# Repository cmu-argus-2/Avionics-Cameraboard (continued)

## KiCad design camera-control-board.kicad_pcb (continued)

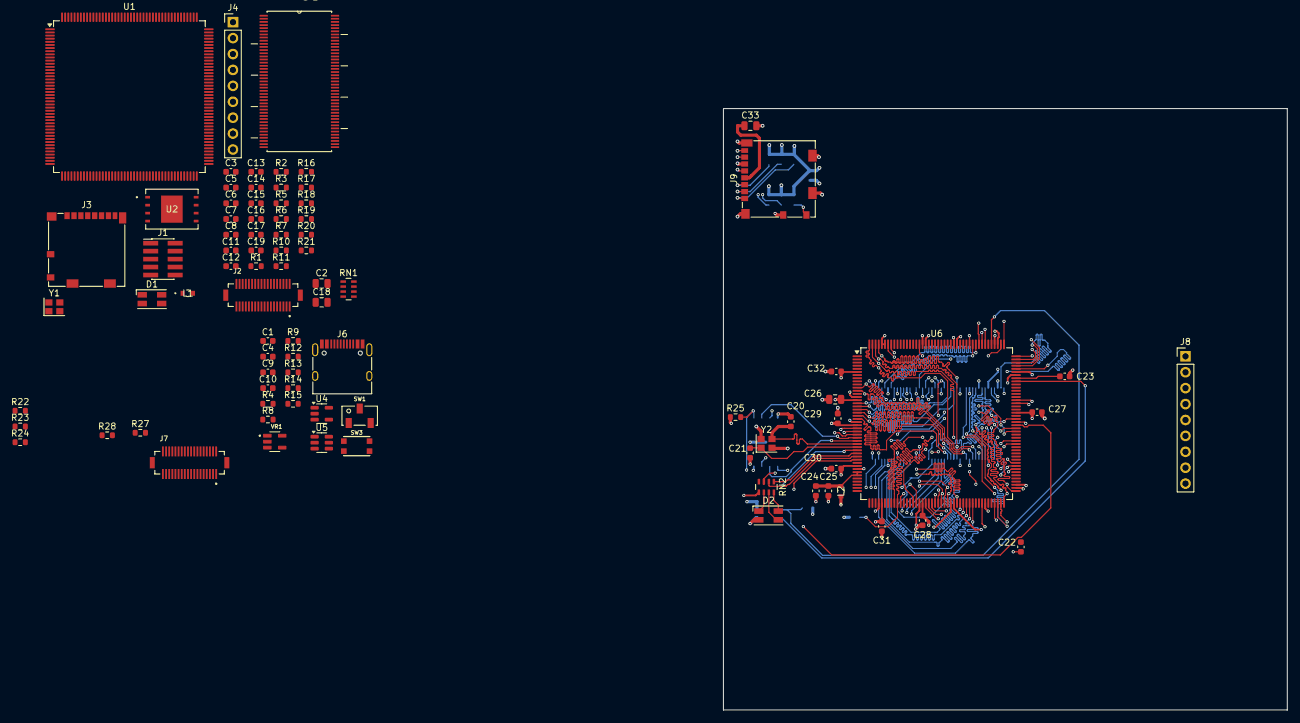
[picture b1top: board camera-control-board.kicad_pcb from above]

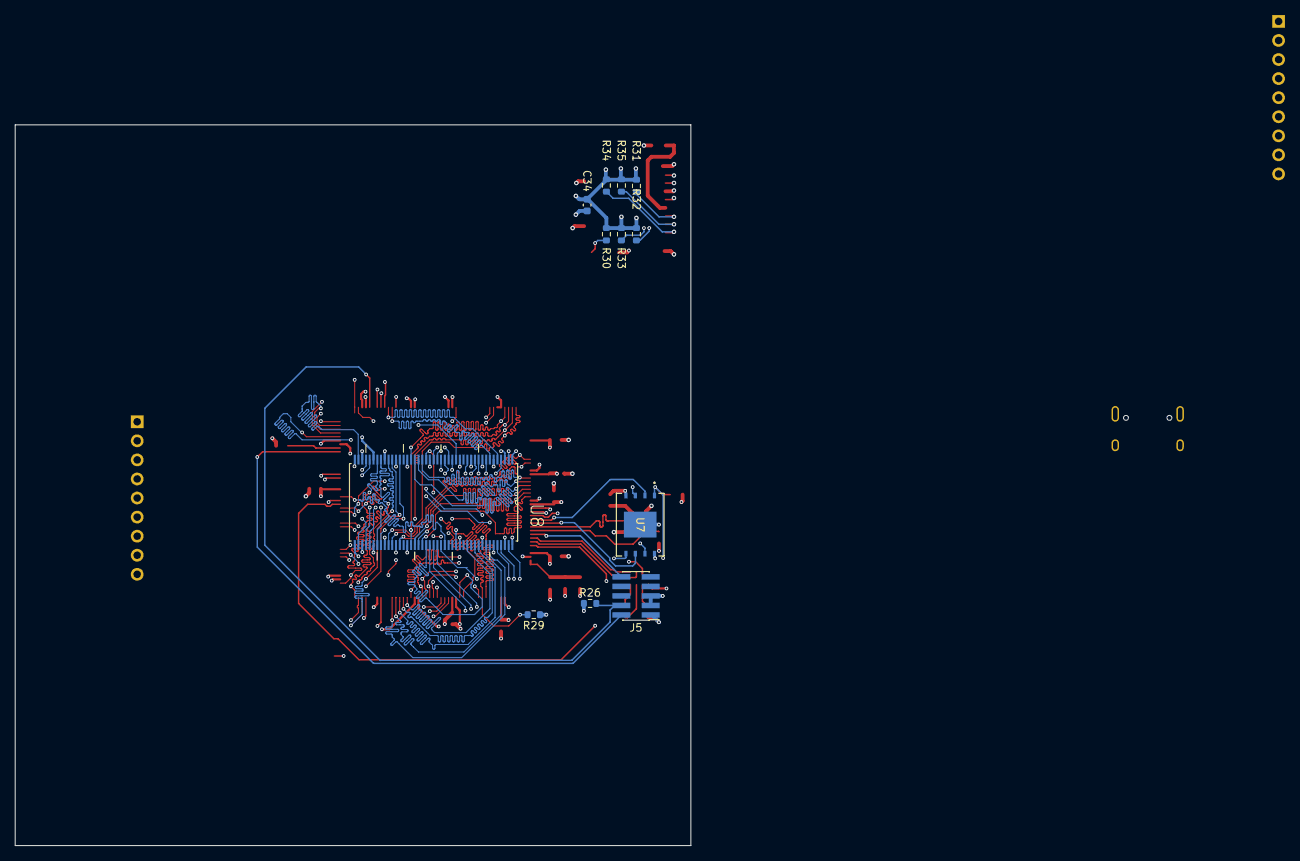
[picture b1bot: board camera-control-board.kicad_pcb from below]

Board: 6 copper layers, 90.0 x 96.0 mm, 97 parts (12 on the bottom side), 237 nets.

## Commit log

2024-09-27 Began creating schematic for RT1062. More to come.
2024-09-28 Some updates
2024-09-28 New Schematic Completed. Updated README.
    New schematic completed. Finished the new STM32 to SDRAM and Image Sensor Connections.
2024-09-29 Changed IC, began USB.
    I changed the correct IC, attempted to add USB. Want to make sure that we have the voltage protection circuit, not sure exactly how it works, will check soon.
2024-09-29 Removed USB Protection, added SD Card Circuit
2024-10-02 verify libs
2024-10-02 reformatting repo (backed up locally)
2024-10-02 adding gitignore
2024-10-02 adding kicad librarires
2024-10-02 added files
2024-10-02 configured library and repo correctly. edits incoming
2024-10-03 adding LDOs, changed schematic sheet size
2024-10-03 Most of revisions finished. Added Flash.
2024-10-03 Schematic Revs Finished.
2024-10-03 all footprints accounted for.
2024-10-04 Layout begun.
2024-10-04 Layout ~1/3rd done
2024-10-04 attempting layout on diff branch
2024-10-05 layout 45deg
2024-10-05 added 3v3, GND routing
2024-10-06 First half routed, impedance matching now
2024-10-06 AAAAAAAAAAAAAAAAAH
2024-10-06 all first half impedance matched...,.
2024-10-06 all traces routed, impedance matching fight begins
2024-10-06 all SDRAM traces laid out and length matched.
2024-10-06 All SDRAM traces complete.
2024-10-06 weird change (github is telling me to)
2024-10-06 Updated to add USB-C Connection.
2024-10-06 added USB C connection
2024-10-07 shhh fixed lowkey wrong trace sizes
2024-10-07 SD Card routed (theoretically), now adding connector.
2024-10-07 commit just to be sure
2024-10-08 Finished connector.
2024-10-08 image sensor routed
2024-10-08 flash memory routed.
2024-10-08 going to update pcb from schematic (will report back)
2024-10-09 Layout finished; DRC checks next.
2024-10-09 DRC Clean*
2024-10-10 Minor Schematic cleanup
2024-10-10 begun power tracing
2024-10-12 Added a single hole
2024-10-19 added schematic for second set. Layout? Who's she..?
2024-10-20 RAM Under MCU Routed, Length Matching Next... uh oh
2024-10-20 Some traces Length-Matched. Come back and do bottom line restructuring.
2024-10-20 cont-push
2024-10-20 All traces length-matched. HUZZAH!
2024-10-20 pos change
2024-10-21 Lots more layout, image sensor + a few resistors left
